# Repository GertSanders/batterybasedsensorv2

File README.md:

# batterybasedsensorv2
An atmega328p based board for battery based sensors. Software is based on the MySensors library. This repo is for the hardware of my board. Design was done in CADSoft Eagle 7.3 (free light version).

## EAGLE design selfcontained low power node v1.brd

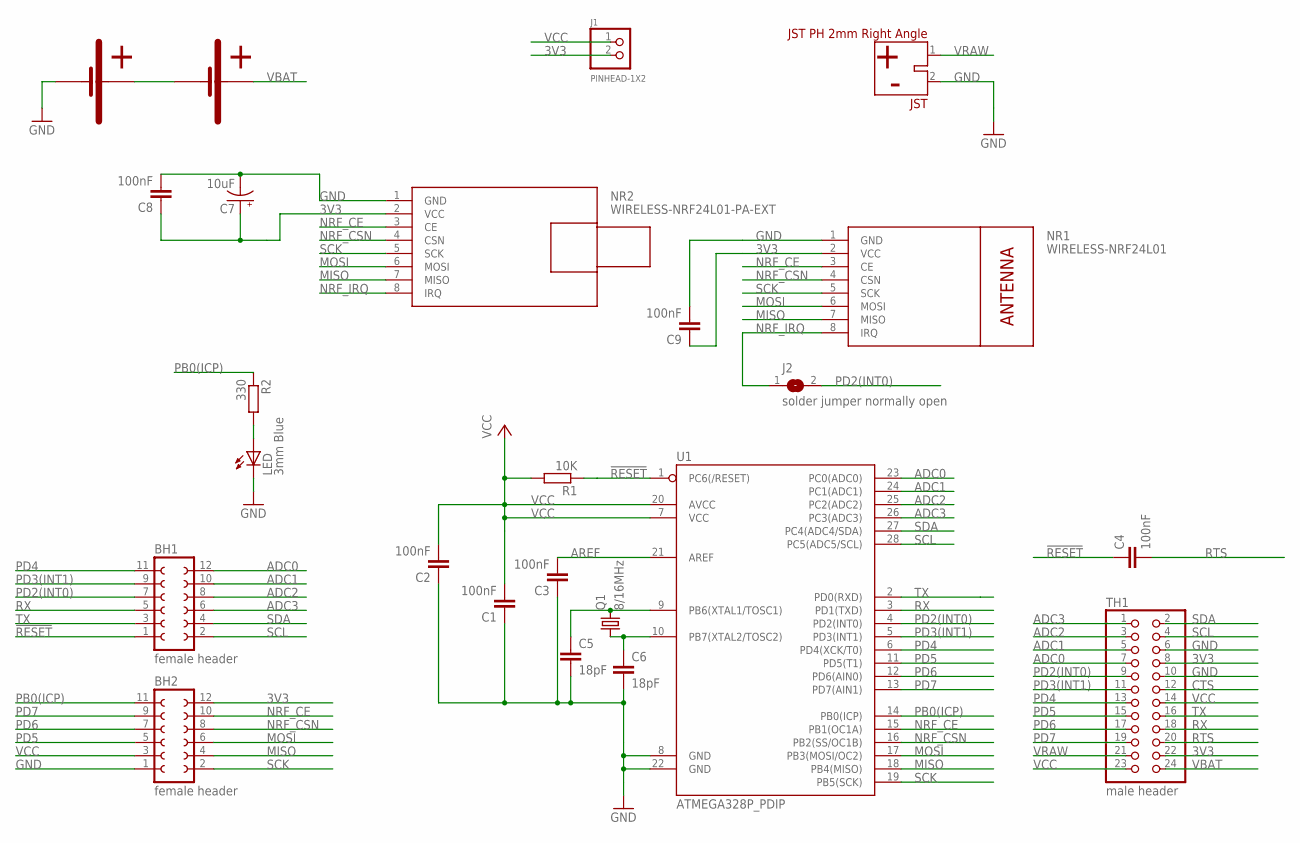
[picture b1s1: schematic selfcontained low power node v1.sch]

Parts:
BAT1, BAT2: AAABATTERY; AAABATTERYHOLDER
BH1, BH2: female header; FE06-2
C1, C2, C3, C4, C8, C9: 100nF; C025-025X050
C5, C6: 18pF; C025_050-024X070
C7: 10uF; E2,5-5
J1: PINHEAD-1X2; PIHEAD-1X2
J2: solder jumper normally open; SJ
JST: JST PH 2mm Right Angle; JST-PH-2-THM-RA
LED: 3mm Blue; LED3MM
NR1: WIRELESS-NRF24L01
NR2: WIRELESS-NRF24L01-PA-EXT; WIRELESS-NRD24L01-PA-EXT
Q1: 8/16MHz; HC49/S
R1: 10K; 0207/2V
R2: 330; 0207/2V
TH1: male header; 2X12
U1: ATMEGA328P_PDIP; DIL28-3

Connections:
3V3: BH2.12, C7.+, C8.1, C9.1, J1.2, NR1.2 (VCC), NR2.2 (VCC), TH1.8, TH1.22
!RESET: BH1.1, C4.1, R1.1, U1.1 (PC6(/RESET))
ADC0: BH1.12, TH1.7, U1.23 (PC0(ADC0))
ADC1: BH1.10, TH1.5, U1.24 (PC1(ADC1))
ADC2: BH1.8, TH1.3, U1.25 (PC2(ADC2))
ADC3: BH1.6, TH1.1, U1.26 (PC3(ADC3))
AREF: C3.2, U1.21 (AREF)
CTS: TH1.12
GND: BAT1.P$1, BH2.1, C1.1, C2.1, C3.1, C5.2, C5.3 (2), C6.2, C6.3 (2), C7.-, C8.2, C9.2, JST.2, LED.K (C), NR1.1 (GND), NR2.1 (GND), TH1.6, TH1.10, U1.8 (GND), U1.22 (GND)
MISO: BH2.4, NR1.7 (MISO), NR2.7 (MISO), U1.18 (PB4(MISO))
MOSI: BH2.6, NR1.6 (MOSI), NR2.6 (MOSI), U1.17 (PB3(MOSI/OC2))
unnamed: LED.A, R2.2
unnamed: BAT1.P$2, BAT2.P$1
unnamed: C5.1, Q1.2, U1.9 (PB6(XTAL1/TOSC1))
unnamed: C6.1, Q1.1, U1.10 (PB7(XTAL2/TOSC2))
NRF_CE: BH2.10, NR1.3 (CE), NR2.3 (CE), U1.15 (PB1(OC1A))
NRF_CSN: BH2.8, NR1.4 (CSN), NR2.4 (CSN), U1.16 (PB2(SS/OC1B))
NRF_IRQ: J2.1, NR1.8 (IRQ), NR2.8 (IRQ)
PB0(ICP): BH2.11, R2.1, U1.14 (PB0(ICP))
PD2(INT0): BH1.7, J2.2, TH1.9, U1.4 (PD2(INT0))
PD3(INT1): BH1.9, TH1.11, U1.5 (PD3(INT1))
PD4: BH1.11, TH1.13, U1.6 (PD4(XCK/T0))
PD5: BH2.5, TH1.15, U1.11 (PD5(T1))
PD6: BH2.7, TH1.17, U1.12 (PD6(AIN0))
PD7: BH2.9, TH1.19, U1.13 (PD7(AIN1))
RTS: C4.2, TH1.20
RX: BH1.5, TH1.18, U1.3 (PD1(TXD))
SCK: BH2.2, NR1.5 (SCK), NR2.5 (SCK), U1.19 (PB5(SCK))
SCL: BH1.2, TH1.4, U1.28 (PC5(ADC5/SCL))
SDA: BH1.4, TH1.2, U1.27 (PC4(ADC4/SDA))
TX: BH1.3, TH1.16, U1.2 (PD0(RXD))
VBAT: BAT2.P$2, TH1.24
VCC: BH2.3, C1.2, C2.2, J1.1, R1.2, TH1.14, TH1.23, U1.7 (VCC), U1.20 (AVCC)
VRAW: JST.1, TH1.21

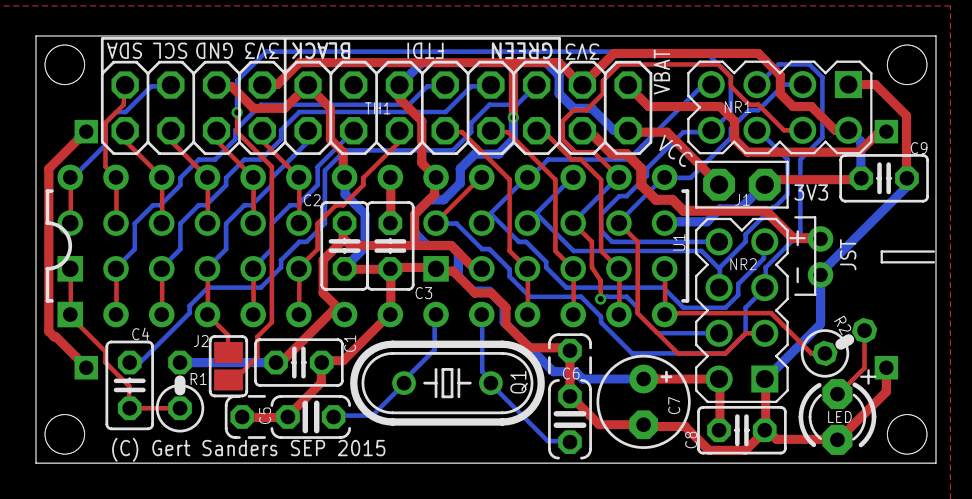
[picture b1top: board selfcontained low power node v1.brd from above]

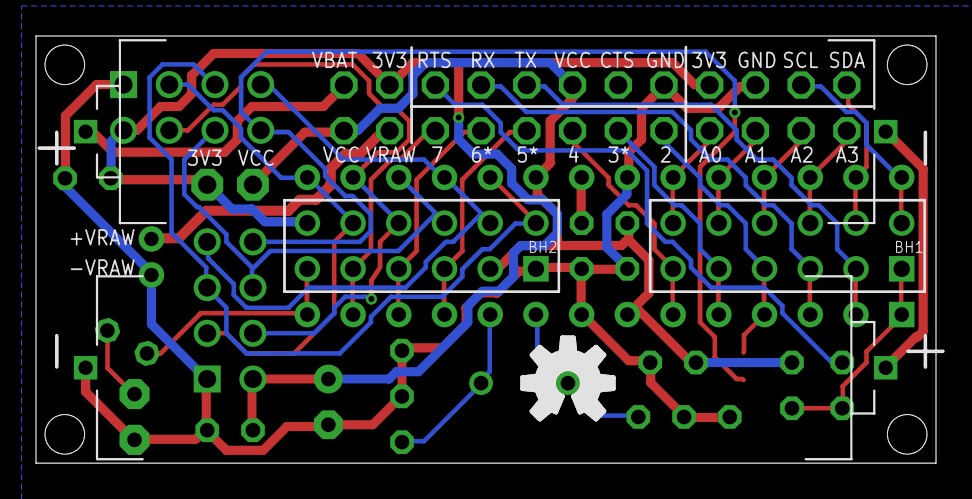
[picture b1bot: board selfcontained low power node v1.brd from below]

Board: 2 copper layers, 50.0 x 23.7 mm, 25 parts (5 on the bottom side), 33 nets.

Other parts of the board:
U$1: OSHWLOGO_TOL_0.2

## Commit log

2015-12-07 Adding EAGLE files
    Adding EAGLE files to repo
2015-12-07 Adding more files
    View of the board and a Bill of Materials
2015-12-07 Even more goodies to add
    Even more goodies to add
